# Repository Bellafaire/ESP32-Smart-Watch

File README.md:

# ESP32 Smartwatch
This project is a fully open source smartwatch based around the ESP32, the project is ongoing for updates see the hackaday.io page for this project (https://hackaday.io/project/168227-custom-smartwatch).
The goal of this project is to create a smartwatch that is easy to reprogram and use as an IOT controller or just as a DIY fashion statement.  
Serial communication and charging are handled on-board through a single micro-usb connector without any external dock. 
The watch is built around the ESP32 WROOM module and is programable using the espressif or Arduino IDE. 
Using the ESP32 allows for the user to develop their software while leveraging the open-source libraries and examples that are available online for quick development.

## Companion App 
The companion android app that allows the smartwatch to control media and obtain phone notifications has been split to a seperate repo and can be found [here](https://github.com/Bellafaire/Android-Companion-App-For-BLE-Devices) along with an example sketch for bluetooth interfacing using the ESP32. 
The app can be downloaded from the releases tab of the provided repo, the V1 watch firmware works only with app releases up to 1.2.0. 
For firmware versions 2 and 3 releases after 2.0.0 must be used, releases after this version use a different communication structure that has proved to be more reliable. 

## Firmware Versions
There are 3 versions of the firmware available for this project. Only V3 is in active development. 
The V1 firmware utilizes deep sleep along with the V1 android companion app, this firmware works well enough and offers the greatest power savings over any of the other options. 
V2 is a bit more animated, boasting some additional applications along with the switch to light sleep which enables faster wakeup from tap or by performing a wrist gesture. 

V3 is the current firmware, it is much more stable and expandable. 
The current V3 firmware supports: 
- App icons on home screen, tap to view the tagline of the notification
- Spotify control through tapping the spotify app icon
- built in calculator 
- Improved UI and tools to aid feature expansion. 

The case is 3D printed and designed in FreeCAD, the design files are available in this repo. 

### Dependencies 
If you're working with the V3 Firmware, then you will need the following dependencies, you can get these through the Arduino IDE library manager: 
- Adafruit GFX Version 1.11.9 By Adafruit
- Adafruit ST7735 and ST7789 Library Version 1.10.3 By Adafruit
- base64 Version 1.30 by Densaugeo 

Other versions of the above dependencies **will most likely work** but have not been tested on this hardware. 

## Hardware Versions
The current hardware version for the watch is V5 which provides a more slim design while maintaining all the features of V4. 

## Video Updates about the project

[Video Update #5](https://www.youtube.com/watch?v=LVs-HgjjFUM)

[Video Update #4](https://www.youtube.com/watch?v=E8-lO0pQunM)

[Video Update #3](https://www.youtube.com/watch?v=vvuce4NQqrk)

[Video Update #2](https://www.youtube.com/watch?v=UNLAq5FuJq4)

[Video Update #1](https://www.youtube.com/watch?v=IoVqdB_q3pE)

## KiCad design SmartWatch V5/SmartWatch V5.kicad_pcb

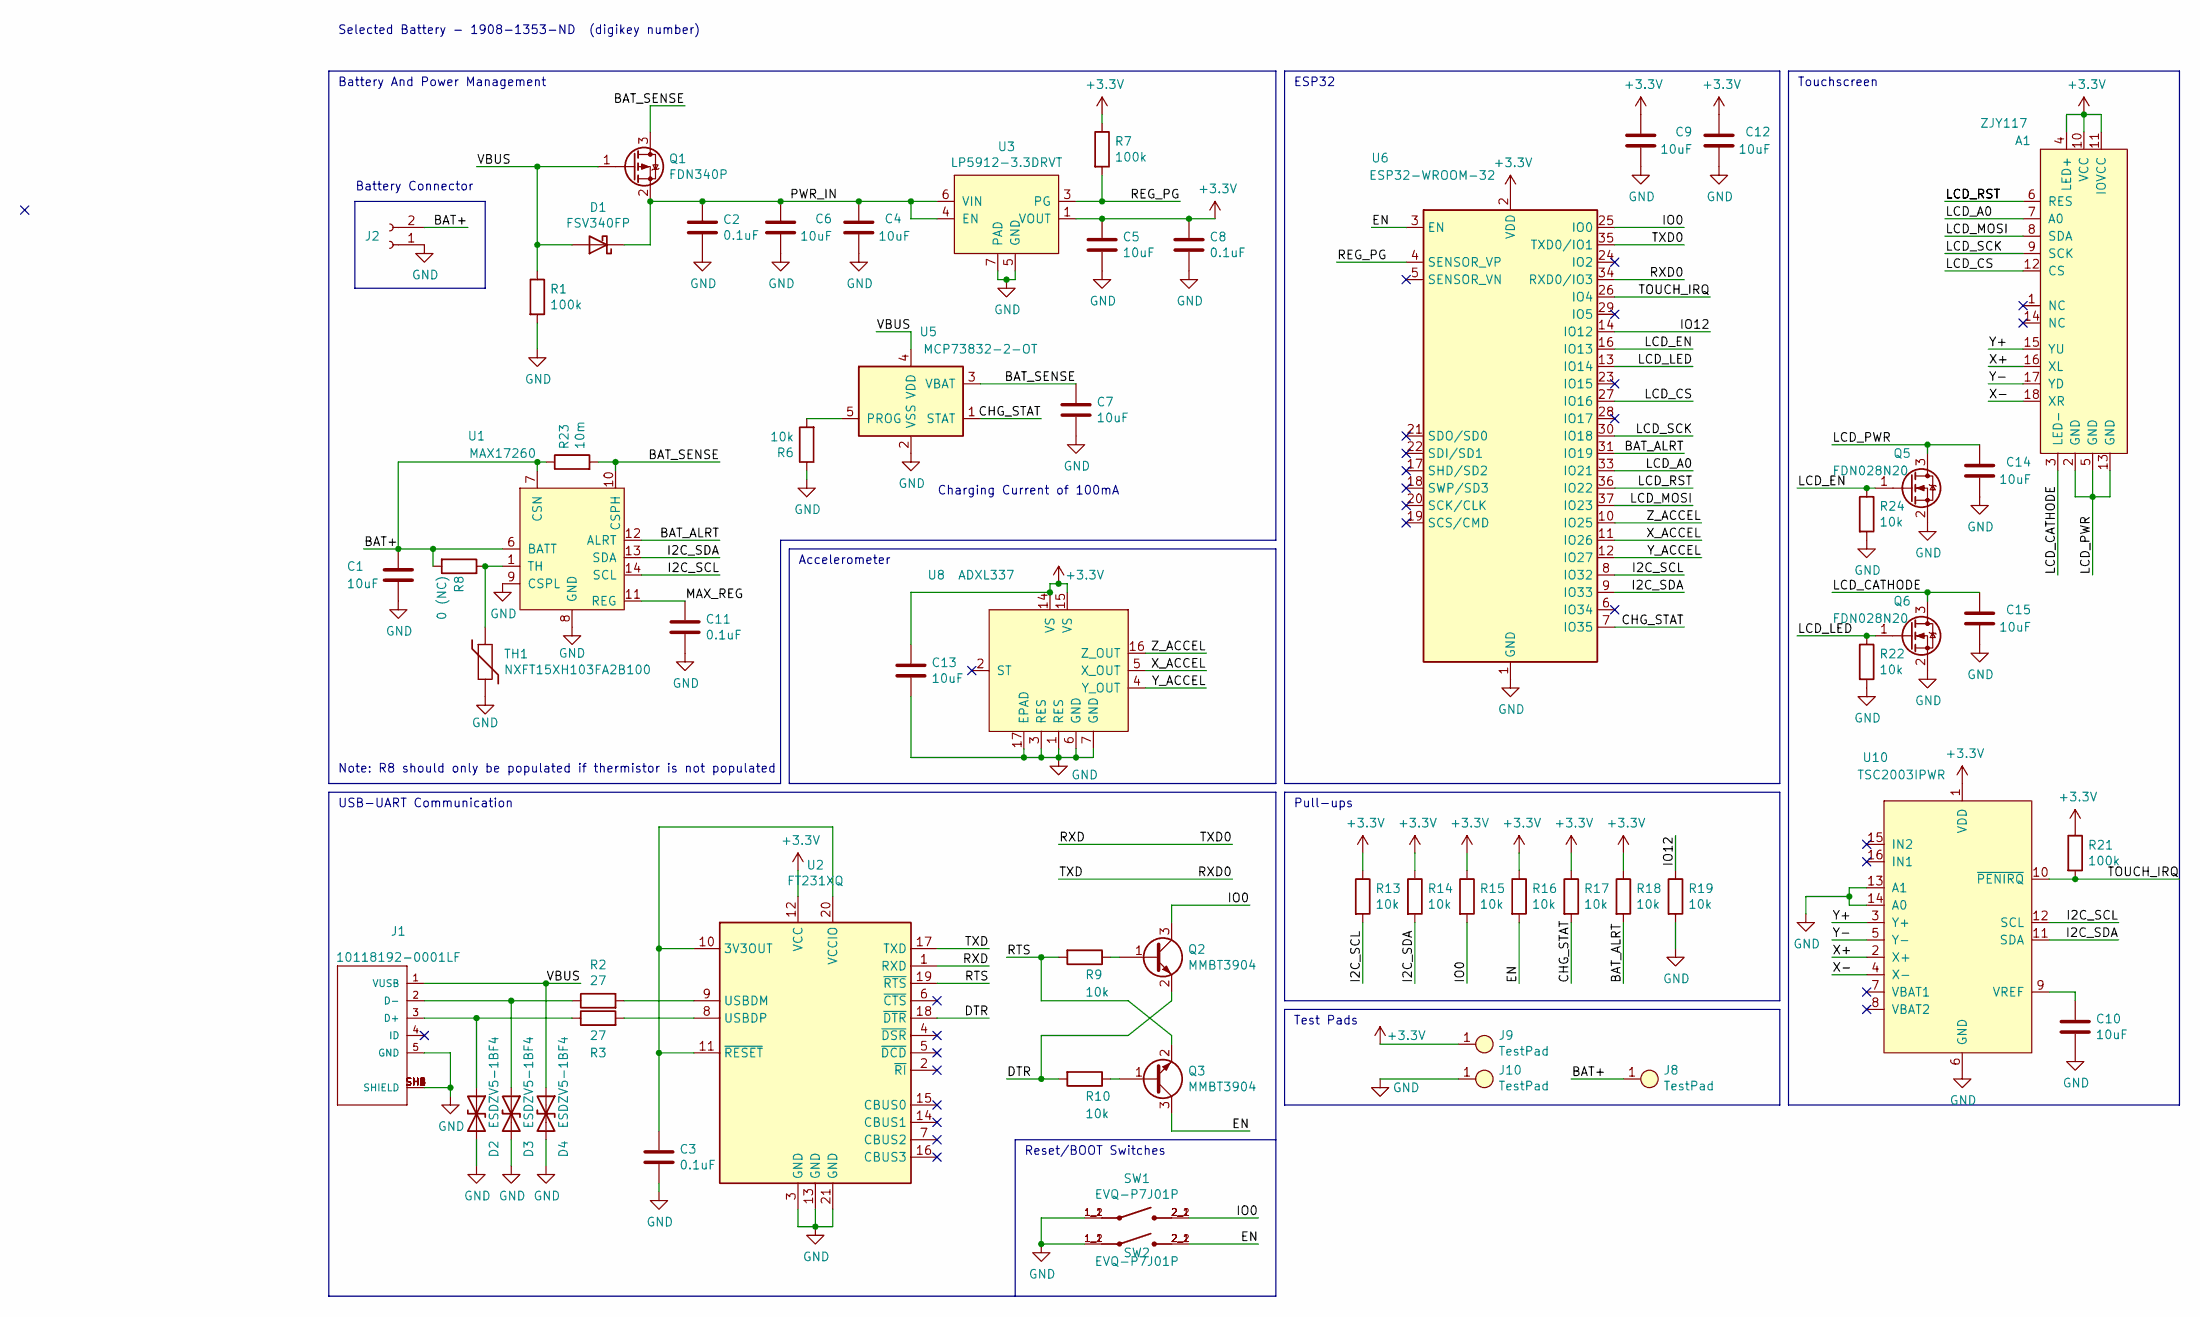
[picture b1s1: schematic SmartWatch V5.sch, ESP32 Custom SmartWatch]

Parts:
A1: ZJY117
C1, C4, C5, C6, C7, C9, C10, C12, C13, C14, C15: 10uF; C_0603_1608Metric; digikey 478-10766-1-ND
C2, C3, C8, C11: 0.1uF; C_0603_1608Metric; digikey 1276-1006-1-ND
D1: FSV340FP; D_SOD-123; digikey FSV340FPCT-ND
D2, D3, D4: ESDZV5-1BF4; D_0201_0603Metric; digikey 497-17318-1-ND
J1: 10118192-0001LF; AMPHENOL_10118192-0001LF; digikey 609-4613-1-ND
J2: BATTERY
J8, J9, J10: TestPad; TESTPAD
Q1: FDN340P; SOT-23; digikey FDN340PCT-ND
Q2, Q3: MMBT3904; SOT-23; digikey 1727-4044-1-ND
Q5, Q6: FDN028N20; SOT-23; digikey FDN028N20OSCT-ND
R1, R7, R21: 100k; R_0603_1608Metric; digikey CR0603-JW-104ELFCT-ND
R2, R3: 27; R_0603_1608Metric; digikey RMCF0603JT27R0CT-ND
R6, R9, R10, R13, R14, R15, R16, R17, R18, R19, R22, R24: 10k; R_0603_1608Metric; digikey 311-10.0KCRCT-ND
R8: 0 (NC); R_0603_1608Metric; digikey 311-0.0GRCT-ND
R23: 10m; R_0805_2012Metric; digikey RL12T.010JCT-ND
SW1, SW2: EVQ-P7J01P; SW_EVQ-P7J01P; digikey P16767CT-ND
TH1: NXFT15XH103FA2B100; PinHeader_1x02_P1.00mm_Vertical; digikey 490-5630-ND
U1: MAX17260; TDFN16-EP; digikey 175-MAX17260SEWL+TCT-ND
U2: FT231XQ; QFN-20-1EP_4x4mm_P0.5mm_EP2.5x2.5mm; digikey 768-1128-1-ND
U3: LP5912-3.3DRVT; WSON-6-1EP_2x2mm_P0.65mm_EP1x1.6mm_ThermalVias; digikey 296-44153-1-ND
U5: MCP73832-2-OT; SOT-23-5; digikey MCP73832T-2ACI/OTCT-ND
U6: ESP32-WROOM-32; digikey 1904-1010-1-ND
U8: ADXL337; ADXL337BCPZ-RL; digikey ADXL337BCPZ-RLCT-ND
U10: TSC2003IPWR; TSSOP-16_4.4x5mm_P0.65mm; digikey 296-14340-1-ND

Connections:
+3V3: A1.4 (LED+), A1.10 (VCC), A1.11 (IOVCC), C5.1, C8.1, C9.1, C12.1, C13.1, J9.1, R7.1, R13.1, R14.1, R15.1, R16.1, R17.1, R18.1, R21.1, U2.12 (VCC), U3.1 (VOUT), U6.2 (VDD), U8.14 (VS), U8.15 (VS), U10.1 (VDD)
/BAT+: C1.1, J2.2, J8.1, R8.2, R23.1, U1.6 (BATT), U1.7 (CSN)
/BAT_ALRT: R18.2, U1.12 (ALRT), U6.31 (IO19)
/BAT_SENSE: C7.1, Q1.3 (D), R23.2, U1.10 (CSPH), U5.3 (VBAT)
/CHG_STAT: R17.2, U5.1 (STAT), U6.7 (IO35)
/DTR: Q2.2 (E), R10.2, U2.18 (~DTR)
/EN: Q3.3 (C), R16.2, SW2.2_1 (2), SW2.2_2 (2), U6.3 (EN)
/I2C_SCL: R13.2, U1.14 (SCL), U6.8 (IO32), U10.12 (SCL)
/I2C_SDA: R14.2, U1.13 (SDA), U6.9 (IO33), U10.11 (SDA)
/IO0: Q2.3 (C), R15.2, SW1.2_1 (2), SW1.2_2 (2), U6.25 (IO0)
/IO12: R19.1, U6.14 (IO12)
/LCD_A0: A1.7 (A0), U6.33 (IO21)
/LCD_CATHODE: A1.3 (LED-), C15.1, Q6.3 (D)
/LCD_CS: A1.12 (CS), U6.27 (IO16)
/LCD_EN: Q5.1 (G), R24.1, U6.16 (IO13)
/LCD_LED: Q6.1 (G), R22.1, U6.13 (IO14)
/LCD_MOSI: A1.8 (SDA), U6.37 (IO23)
/LCD_PWR: A1.2 (GND), A1.5 (GND), A1.13 (GND), C14.1, Q5.3 (D)
/LCD_RST: A1.6 (RES), U6.36 (IO22)
/LCD_SCK: A1.9 (SCK), U6.30 (IO18)
/MAX_REG: C11.1, U1.11 (REG)
/PWR_IN: C2.1, C4.1, C6.1, D1.1 (K), Q1.2 (S), U3.4 (EN), U3.6 (VIN)
/REG_PG: R7.2, U3.3 (PG~), U6.4 (SENSOR_VP)
/RTS: Q3.2 (E), R9.2, U2.19 (~RTS)
/RXD: U2.1 (RXD), U6.35 (TXD0/IO1)
/RXD0: U2.17 (TXD), U6.34 (RXD0/IO3)
/TOUCH_IRQ: R21.2, U6.26 (IO4), U10.10 (~PENIRQ~)
/VBUS: D1.2 (A), D4.1 (A1), J1.1 (VUSB), Q1.1 (G), R1.1, U5.4 (VDD)
/X+: A1.16 (XL), U10.2 (X+)
/X-: A1.18 (XR), U10.4 (X-)
/X_ACCEL: U6.11 (IO26), U8.5 (X_OUT)
/Y+: A1.15 (YU), U10.3 (Y+)
/Y-: A1.17 (YD), U10.5 (Y-)
/Y_ACCEL: U6.12 (IO27), U8.4 (Y_OUT)
/Z_ACCEL: U6.10 (IO25), U8.16 (Z_OUT)
GND: C1.2, C2.2, C3.2, C4.2, C5.2, C6.2, C7.2, C8.2, C9.2, C10.2, C11.2, C12.2, C13.2, C14.2, C15.2, D2.2 (A2), D3.2 (A2), D4.2 (A2), J1.5 (GND), J1.SH1 (SHIELD), J1.SH2 (SHIELD), J1.SH3 (SHIELD), J1.SH4 (SHIELD), J1.SH5 (SHIELD), J1.SH6 (SHIELD), J2.1, J10.1, Q5.2 (S), Q6.2 (S), R1.2, R6.1, R19.2, R22.2, R24.2, SW1.1_1 (1), SW1.1_2 (1), SW2.1_1 (1), SW2.1_2 (1), TH1.2, U1.8 (GND), U1.9 (CSPL), U1.15 (EP), U2.3 (GND), U2.13 (GND), U2.21 (GND), U3.5 (GND), U3.7 (PAD), U5.2 (VSS), U6.1 (GND), U6.15 (GND), U6.38 (GND), U6.39 (GND), U8.1 (RES), U8.3 (RES), U8.6 (GND), U8.7 (GND), U8.17 (EPAD), U10.6 (GND), U10.13 (A1), U10.14 (A0)
unnamed: C3.1, U2.10 (3V3OUT), U2.11 (~RESET), U2.20 (VCCIO)
unnamed: C10.1, U10.9 (VREF)
unnamed: D2.1 (A1), J1.3 (D+), R3.1
unnamed: D3.1 (A1), J1.2 (D-), R2.1
unnamed: Q2.1 (B), R9.1
unnamed: Q3.1 (B), R10.1
unnamed: R2.2, U2.9 (USBDM)
unnamed: R3.2, U2.8 (USBDP)
unnamed: R6.2, U5.5 (PROG)
unnamed: R8.1, TH1.1, U1.1 (TH)

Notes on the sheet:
Pull-ups
Test Pads
Battery And Power Management
Battery Connector
Reset/BOOT Switches
ESP32
Touchscreen
USB-UART Communication
Charging Current of 100mA
Note: R8 should only be populated if thermistor is not populated
Selected Battery - 1908-1353-ND (digikey number)
Accelerometer

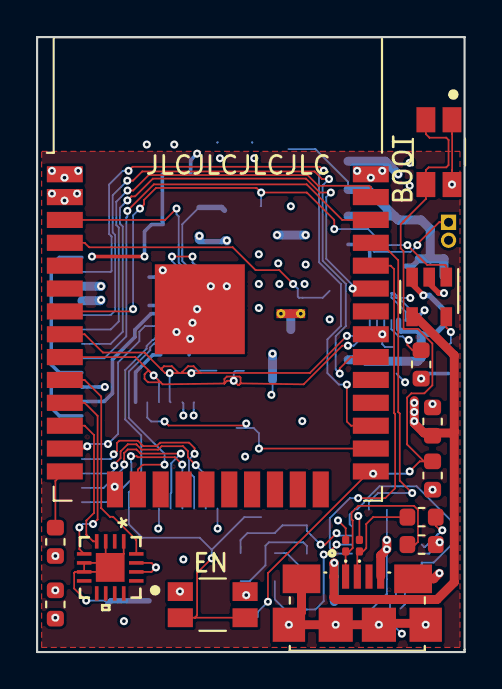
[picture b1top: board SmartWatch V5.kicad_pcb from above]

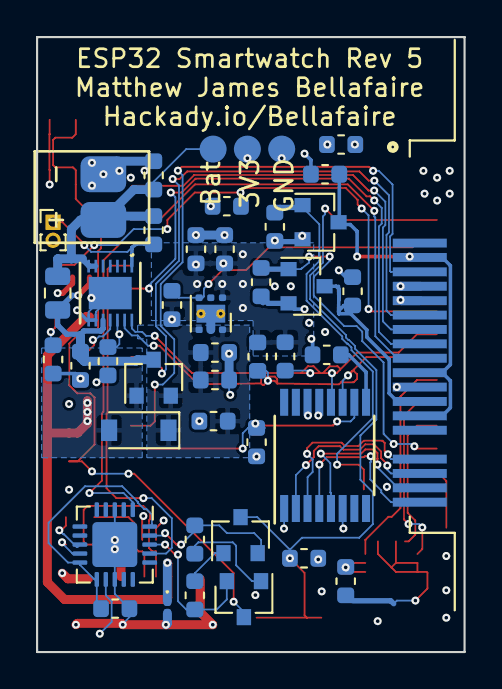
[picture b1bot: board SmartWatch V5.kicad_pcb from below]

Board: 4 copper layers, 23.7 x 34.2 mm, 59 parts (44 on the bottom side), 46 nets.

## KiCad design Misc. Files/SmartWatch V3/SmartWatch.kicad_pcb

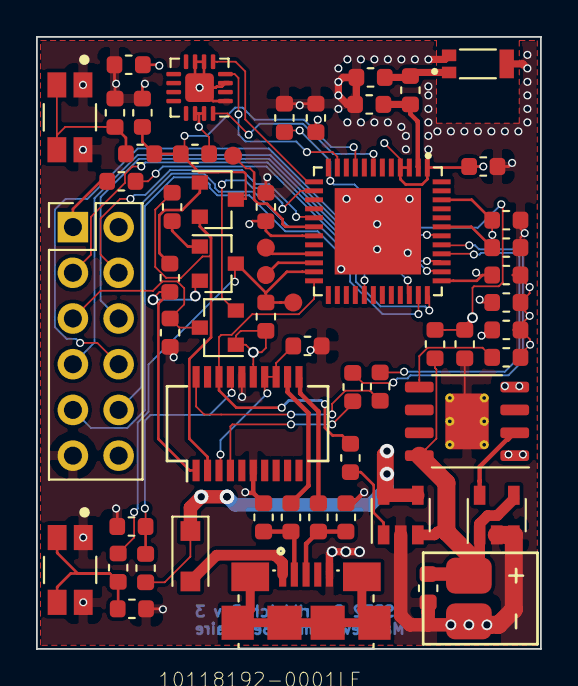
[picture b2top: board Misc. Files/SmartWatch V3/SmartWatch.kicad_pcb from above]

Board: 4 copper layers, 28.0 x 34.0 mm, 58 parts (0 on the bottom side), 48 nets.

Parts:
ANT1: W3008; ANTENNA_W3008
C1, C2: 10nF; C_0603_1608Metric
C3, C20: 10uF; C_0603_1608Metric
C4: 0.1uF; C_0603_1608Metric
C5, C7, C9, C11, C15, C16, C17, C18, C19: 0.1u; C_0603_1608Metric
C6: 0.1u (NC); C_0603_1608Metric
C8, C14: 47p; C_0603_1608Metric
C10: 10u; C_0603_1608Metric
C12, C13: TBD; C_0603_1608Metric
D2: FSV340FP; D_SOD-123F
ESP1: ESP32PICO_D4-esp32pico_d4; ESP32_D4_PICO_HAND_SOLDER
J1: 10118192-0001LF; AMPHENOL_10118192-0001LF
J2: Bat_in; BATTERY
J3, J4, J5, J6: TEST_PAD
L1: TBD; L_0603_1608Metric
Q1, Q2: MMBT3904; SOT-23
Q3: FDN340P; SOT-23
R1, R2, R3, R4, R8, R19: 0R; R_0603_1608Metric
R5, R6, R7, R11, R13, R14, R15, R16: 10k; R_0603_1608Metric
R9, R10: 27; R_0603_1608Metric
R12: 47k; R_0603_1608Metric
SW1, SW2: EVQ-P7J01P; SW_EVQ-P7J01P
U1: S-13A1A33-E8T1U3; HSOP-8-1EP_3.9x4.9mm_P1.27mm_EP2.41x3.1mm_ThermalVias
U2: LCD_TOUCH; PinHeader_2x06_P2.54mm_Vertical
U3: FT231XS; SSOP-20_3.9x8.7mm_P0.635mm
U4: MAX9065; SOT-23-5
U5: MCP73811T-420I-OT; SOT-23-5
U7: ADXL337; LFCSP-16-1EP_3x3mm_P0.5mm_EP1.6x1.6mm

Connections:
+3V3: C2.1, C3.1, C9.1, C10.1, C11.1, C16.1, C17.1, C18.1, C19.1, ESP1.1, ESP1.3, ESP1.4, ESP1.19, ESP1.37, ESP1.43, ESP1.46, Q3.1, R14.2, R15.1, U1.1, U2.12, U3.15, U7.14, U7.15
/Charge_Enable: ESP1.24, R1.1, U3.18
/ESP32 Pico D4/DTR: Q1.2, R7.1, U3.1
/ESP32 Pico D4/EN: C15.1, ESP1.9, Q2.3, R14.1, R19.1
/ESP32 Pico D4/ESP32_RX: ESP1.40, R3.2
/ESP32 Pico D4/ESP32_TX: ESP1.41, R2.2
/ESP32 Pico D4/IO0: ESP1.23, J3.1, Q1.3, R8.1, R15.2
/ESP32 Pico D4/IO2: ESP1.22, J4.1
/ESP32 Pico D4/IO12: ESP1.18, J6.1
/ESP32 Pico D4/IO15: ESP1.21, J5.1
/ESP32 Pico D4/IO32: C5.1, ESP1.12, R6.1, R11.2
/ESP32 Pico D4/LNA_IN: C13.2, ESP1.2, L1.1
/ESP32 Pico D4/RTS: Q2.2, R5.1, U3.2
/ESP32 Pico D4/RXD: R2.1, U3.4
/ESP32 Pico D4/TXD: R3.1, U3.20
/ESP32 Pico D4/USB_DN: C8.1, J1.2, R9.1
/ESP32 Pico D4/USB_DP: C14.1, J1.3, R10.2
/LCD_A0: ESP1.42, U2.8
/LCD_CS: ESP1.34, U2.3
/LCD_LED: Q3.3, R16.2, U2.5
/LCD_LED_CTRL: ESP1.14, Q3.2
/LCD_PEN: ESP1.29, R4.2
/LCD_RST: ESP1.39, U2.7
/LCD_SCK: ESP1.35, U2.9
/MISO: ESP1.38, U2.6
/MOSI: ESP1.36, U2.10
/TOUCH_CS: ESP1.17, U2.4
BAT+: C20.1, J2.2, R6.2, U1.8, U4.1, U4.4, U5.3
GND: ANT1.G1, ANT1.G2, C1.2, C2.2, C3.2, C4.2, C5.2, C6.2, C7.2, C8.2, C9.2, C10.2, C11.2, C12.2, C14.2, C15.2, C16.2, C17.2, C18.2, C19.2, C20.2, ESP1.49, J1.5, J2.1, L1.2, R11.1, R13.1, R16.1, SW1.1_1, SW1.1_2, SW2.1_1, SW2.1_2, U1.4, U1.9, U2.11, U3.6, U3.16, U4.2, U4.3, U5.2, U7.1, U7.3, U7.6, U7.7, U7.17
unnamed: ANT1.FEED, C12.1, C13.1
unnamed: C1.1, U1.5
unnamed: C4.1, U3.3, U3.13, U3.14
unnamed: C6.1, R8.2, SW1.2_1, SW1.2_2
unnamed: C7.1, R19.2, SW2.2_1, SW2.2_2
unnamed: D2.2, J1.1
unnamed: J1.SH1, J1.SH2, J1.SH3, J1.SH4, J1.SH5, J1.SH6
unnamed: Q1.1, R5.2
unnamed: Q2.1, R7.2
unnamed: R1.2, U5.1
unnamed: R4.1, U2.1
unnamed: R9.2, U3.12
unnamed: R10.1, U3.11
unnamed: R12.1, R13.2, U3.17
UV_LO: U1.2, U4.5
VUSB: D2.1, R12.2, U5.4, U5.5
X_SIG: ESP1.13, U7.5
Y_SIG: ESP1.11, U7.4
Z_SIG: ESP1.7, U7.16

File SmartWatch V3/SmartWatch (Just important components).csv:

Qty,Reference(s),Value,LibPart,Footprint,Datasheet,DigiKey Part Number
1,ANT1,W3008,SmartWatch-rescue:W3008,SmartWatch:ANTENNA_W3008,Manufacturer recommendations,553-1530-1-ND
2,"C1, C2",10nF,Device:C,Capacitor_SMD:C_0603_1608Metric,~,399-7842-1-ND
25,"C3, C20",10uF,Device:C,Capacitor_SMD:C_0603_1608Metric,~,478-10766-1-ND
50,"C5, C7, C9, C11, C15, C16, C17, C18, C19",0.1u,Device:C,Capacitor_SMD:C_0603_1608Metric,~,1276-1258-1-ND
3,ESP1,ESP32PICO_D4-esp32pico_d4,SmartWatch-rescue:ESP32PICO_D4-esp32pico_d4,SmartWatch:ESP32_D4_PICO_HAND_SOLDER,,1904-1029-1-ND
50,"Q1, Q2",MMBT3904,Transistor_BJT:MMBT3904,Package_TO_SOT_SMD:SOT-23,https://www.fairchildsemi.com/datasheets/2N/2N3904.pdf,MMBT3904TPMSCT-ND
6,"R1, R2, R3, R4, R8, R19",0R,Device:R,Resistor_SMD:R_0603_1608Metric,~,311-0.0GRCT-ND
8,"R5, R6, R7, R11, R13, R14, R15, R16",10k,Device:R,Resistor_SMD:R_0603_1608Metric,~,311-10KGRCT-ND
2,"R9, R10",27,Device:R,Resistor_SMD:R_0603_1608Metric,~,311-27.0HRCT-ND
1,R12,47k,Device:R,Resistor_SMD:R_0603_1608Metric,~,311-47GRCT-ND
10,"SW1, SW2",EVQ-P7J01P,SmartWatch-rescue:EVQ-P7J01P,SmartWatch:SW_EVQ-P7J01P,Panasonic,P16767CT-ND
2,U1,S-13A1A33-E8T1U3,SmartWatch-rescue:S-13A1A33-E8T1U3,Package_SO:HSOP-8-1EP_3.9x4.9mm_P1.27mm_EP2.41x3.1mm_ThermalVias,https://www.ablic.com/en/doc/datasheet/voltage_regulator/S13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,1662-2801-1-ND
3,U3,FT231XS,Interface_USB:FT231XS,Package_SO:SSOP-20_3.9x8.7mm_P0.635mm,http://www.ftdichip.com/Products/ICs/FT231X.html,768-1129-1-ND

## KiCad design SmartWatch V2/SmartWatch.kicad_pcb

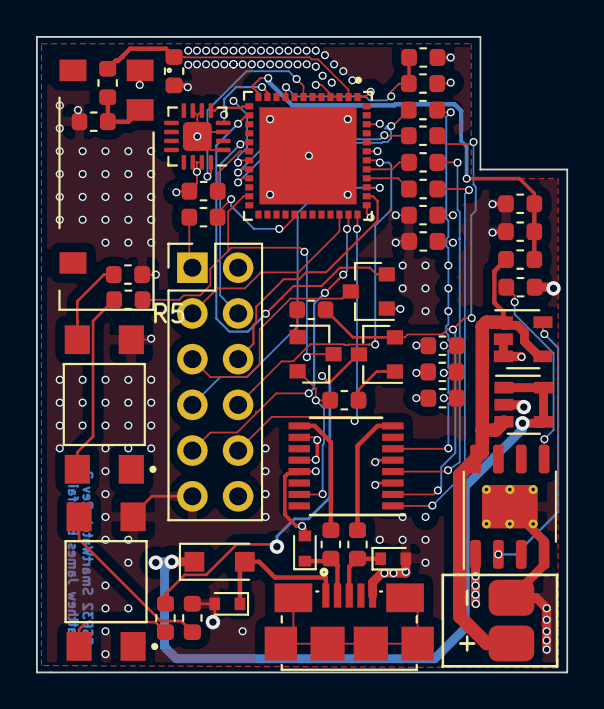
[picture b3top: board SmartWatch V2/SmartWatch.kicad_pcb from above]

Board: 4 copper layers, 29.5 x 35.3 mm, 47 parts (0 on the bottom side), 49 nets.

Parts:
C1, C2: 10nF; C_0603_1608Metric
C3: 10uF; C_0603_1608Metric
C4, C10: 10u; C_0603_1608Metric
C5, C7, C9, C11: 0.1u; C_0603_1608Metric
C6: 0.1u (NC); C_0603_1608Metric
C12: 2.7pF; C_0603_1608Metric
C13: 4.7pF; C_0603_1608Metric
D1, D3, D4: LESD5D5.0CT1G; D_SOD-523
D2: FSV340FP; D_SOD-123F
J1: 10118192-0001LF; AMPHENOL_10118192-0001LF
J2: Bat_in; BATTERY
J3: Conn_01x04; ANT_PRO-OB-440
L1: 1.6nH; L_0603_1608Metric
Q2, Q4: MMBT5551L; SOT-23
Q3: FDN340P; SOT-23
R1, R2, R13, R14: 1k; R_0603_1608Metric
R4, R8, R19: 0R; R_0603_1608Metric
R5, R7: 0(NC); R_0603_1608Metric
R6, R11, R20, R22: 10k; R_0603_1608Metric
R9, R10: 0; R_0603_1608Metric
SW4, SW5: TL3305AF260QG; SW_TL3305AF260QG
U1: S-13A1A33-E8T1U3; HSOP-8-1EP_3.9x4.9mm_P1.27mm_EP2.41x3.1mm_ThermalVias
U2: LCD_TOUCH; PinHeader_2x06_P2.54mm_Vertical
U3: FT230XS; SSOP-16_3.9x4.9mm_P0.635mm
U4: MAX9065; SOT-23-5
U5: MCP73811T-420I-OT; SOT-23-5
U7: ADXL337; LFCSP-16-1EP_3x3mm_P0.5mm_EP1.6x1.6mm
U12: ESP32-PICO-D4; PQFN50P700X700X104-49N

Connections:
+3V3: C2.1, C3.1, C4.1, C10.1, C11.1, Q3.1, R20.2, R22.1, U1.1, U2.12, U3.3, U3.10, U3.12, U7.14, U7.15, U12.1, U12.3, U12.4, U12.19, U12.37, U12.43, U12.46
/ESP32 Pico D4/CTS: R7.2, U3.6
/ESP32 Pico D4/DTR: Q4.2, R13.1, U3.15
/ESP32 Pico D4/EN: Q2.3, R19.1
/ESP32 Pico D4/IO0: Q4.3, R8.1, U12.23
/ESP32 Pico D4/IO13: R5.2, U12.20
/ESP32 Pico D4/IO15: R7.1, U12.21
/ESP32 Pico D4/IO32: C5.1, R6.1, R11.2, U12.12
/ESP32 Pico D4/IO36: U12.5, U12.6
/ESP32 Pico D4/LNA_IN: C13.1, L1.2, U12.2
/ESP32 Pico D4/RTS: Q2.2, R5.1, R14.1, U3.2
/ESP32 Pico D4/RXD: R1.1, U3.4
/ESP32 Pico D4/RXD0: R2.2, U12.40
/ESP32 Pico D4/TXD: R2.1, U3.1
/ESP32 Pico D4/TXD0: R1.2, U12.41
/ESP32 Pico D4/USB_DN: R9.2, U3.9
/ESP32 Pico D4/USB_DP: R10.1, U3.8
/LCD_A0: U2.8, U12.42
/LCD_CS: U2.3, U12.34
/LCD_LED: Q3.3, U2.5
/LCD_LED_CTRL: Q3.2, U12.14
/LCD_PEN: R4.2, U12.29
/LCD_RST: U2.7, U12.39
/LCD_SCK: U2.9, U12.35
/MISO: U2.6, U12.38
/MOSI: U2.10, U12.36
/TOUCH_CS: U2.4, U12.17
BAT+: J2.2, R6.2, U1.8, U4.1, U4.4, U5.3
GND: C1.2, C2.2, C3.2, C4.2, C5.2, C6.2, C7.2, C9.2, C10.2, C11.2, C12.2, D1.2, D3.2, D4.2, J1.5, J2.1, J3.1, L1.1, R11.1, SW4.2, SW5.2, U1.4, U1.9, U2.11, U3.5, U3.13, U4.2, U4.3, U5.2, U7.1, U7.3, U7.6, U7.7, U7.17, U12.49
unnamed: C1.1, U1.5
unnamed: C6.1, SW4.4
unnamed: C7.1, SW5.4
unnamed: C9.1, R20.1, U12.9
unnamed: C12.1, C13.2, J3.2
unnamed: D1.1, D2.2, J1.1
unnamed: D3.1, J1.2, R9.1
unnamed: D4.1, J1.3, R10.2
unnamed: J1.SH1, J1.SH2, J1.SH3, J1.SH4, J1.SH5, J1.SH6
unnamed: Q2.1, R13.2
unnamed: Q4.1, R14.2
unnamed: R4.1, U2.1
unnamed: R8.2, SW4.3
unnamed: R19.2, SW5.3
unnamed: R22.2, U12.18
UV_LO: U1.2, U4.5
VUSB: D2.1, U5.1, U5.4, U5.5
X_SIG: U7.5, U12.13
Y_SIG: U7.4, U12.11
Z_SIG: U7.16, U12.7

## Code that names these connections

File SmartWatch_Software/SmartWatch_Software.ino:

/*****************************************************************************
  The MIT License (MIT)

  Copyright (c) 2020 Matthew James Bellafaire

  Permission is hereby granted, free of charge, to any person obtaining a copy
  of this software and associated documentation files (the "Software"), to deal
  in the Software without restriction, including without limitation the rights
  to use, copy, modify, merge, publish, distribute, sublicense, and/or sell
  copies of the Software, and to permit persons to whom the Software is
  furnished to do so, subject to the following conditions:

  The above copyright notice and this permission notice shall be included in all
  copies or substantial portions of the Software.

  THE SOFTWARE IS PROVIDED "AS IS", WITHOUT WARRANTY OF ANY KIND, EXPRESS OR
  IMPLIED, INCLUDING BUT NOT LIMITED TO THE WARRANTIES OF MERCHANTABILITY,
  FITNESS FOR A PARTICULAR PURPOSE AND NONINFRINGEMENT. IN NO EVENT SHALL THE
  AUTHORS OR COPYRIGHT HOLDERS BE LIABLE FOR ANY CLAIM, DAMAGES OR OTHER
  LIABILITY, WHETHER IN AN ACTION OF CONTRACT, TORT OR OTHERWISE, ARISING FROM,
  OUT OF OR IN CONNECTION WITH THE SOFTWARE OR THE USE OR OTHER DEALINGS IN THE
  SOFTWARE.
******************************************************************************/

#include "Declarations.h"

#define uS_TO_S_FACTOR 1000000ULL /* Conversion factor for micro seconds to seconds */
#define TIME_TO_SLEEP 60         /* Time ESP32 will go to sleep (in seconds) */

RTC_DATA_ATTR int bootCount = 0;
RTC_DATA_ATTR boolean YWakeupCondition = false;
RTC_DATA_ATTR int YWakeupCount = 0;

static void RTC_IRAM_ATTR wake_stub();

static void RTC_IRAM_ATTR wake_stub() {

}

//puts device to sleep and configures wakeup sources
void deviceSleep() {
  //re-enable touch wakeup
  esp_sleep_enable_ext0_wakeup(GPIO_NUM_4, 0); //1 = High, 0 = Low
  esp_set_deep_sleep_wake_stub(&wake_stub);
  esp_deep_sleep_start();
}

void setup()
{
  unsigned long wakeupTime = micros();
  unsigned long chrono = micros();
#ifdef DEBUG
  Serial.begin(115200);
#endif
  printDebug("bootCount = " + String(bootCount));

  //init I2C communication
  Wire.begin(I2C_SDA, I2C_SCL, 100000);

  esp_sleep_wakeup_cause_t wakeup_reason;
  wakeup_reason = esp_sleep_get_wakeup_cause();

  pinMode(CHG_STAT, INPUT);
  pinMode(TOUCH_IRQ, INPUT);
  initTouch();

  EEPROM.begin(EEPROM_SIZE);

  if (getBatteryVoltage() < 3.2) {

    printDebug("Battery Voltage is too low to start device: " + String(getBatteryVoltage(), 3));
    pinMode(LCD_LED, OUTPUT);
    pinMode(LCD_EN, OUTPUT);
    digitalWrite(LCD_EN, HIGH);

    for (int a = 0; a < 3; a++) {
      digitalWrite(LCD_LED, HIGH);
      delay(100);
      digitalWrite(LCD_LED, LOW);
      delay(100);
    }



  } else {

    //the battery monitor only needs to be configured once when powered on.
    if (bootCount == 0)
    {
      notificationData[0] = 0;
      initTouch();
      initLCD();
      initBatMonitor();
      testScreen();
      tft.println("phone notifications obtained");
      //      getInternetTime();
      updateTimeFromNotificationData();
      tft.println("obtained time");

      printDebug("Battery Monitor initialized");

    }

    //Check if this is the first reboot and get ready to setup another sleep
    ++bootCount;

    switch (wakeup_reason)
    {
      case ESP_SLEEP_WAKEUP_EXT0:
        deviceActive = true;
        //if woken up by user touching screen
        initTouch();
        initLCD();
        MainLoop();
        break;
      case ESP_SLEEP_WAKEUP_EXT1:
        break;
      case ESP_SLEEP_WAKEUP_TIMER:
        break;
      default:
        printDebug("Wakeup was not caused by deep sleep: " + wakeup_reason);
        break;
    }
  }

  printDebug("Going to sleep now");

#ifdef DEBUG
  printDebug("Awake for " + String(micros() - wakeupTime) + "uS");
  Serial.flush();
#endif

  deviceSleep();
}

void loop()
{
}

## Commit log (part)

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2020-02-24 First Commit of V1 Files
2020-02-24 Commit of Rev3 Board files
    (Currently Working Board)
2020-02-24 Created new design for 3D printed case
2020-02-26 Designed Version 3.2 Case
2020-02-26 Minor changes to main body
2020-02-27 minor change to battery charge code
2020-03-10 added code to keep time in RTC
2020-03-10 changed to verison 0.0.2
2020-03-11 Added notes to schematic for rev 4 changes
2020-03-11 minor comment additions to code and schematic
2020-03-14 comment addition to schematic
2020-03-23 Completed Implementation of Touch Screen
    TODO: Final checks on circuit design
2020-04-08 Completed Electrical Schematic
2020-05-04 Completed work of schematic and board layout of revision 4
    Also began work on new body for the watch
2020-05-11 Changes to version 4 before sending off to production
2020-05-28 Edits
2020-06-05 Finished design of Rev 4.1 board and ordered
    - Also created an I2C device test program to aid assembly and future code
2020-06-15 Started work on software for the project. Basic communication with I2C devices and driving the touch screen
2020-06-15 Ported homescreen code and some interface components from V3 code into the V4 Code
2020-06-15 Implemented settings menu ported from V3
    And changed kiCad schematic to reflect the changes made to the board to resolve charging issue
2020-06-16 added indication that device is charging to the home screen
2020-06-22 Added "option select" window back from previous revision (currently disabled in code)
2020-06-28 Got android app to a semi-working state. uses standard bluetooth to forward notifications to watch
2020-06-28 Rebuilt basic notification reception
2020-06-29 Increaed data grabbed by notification reciever
2020-06-29 added 3 astriks to the end of the data transmission (important for later)
2020-06-29 Added status field and "force bt send" button for debugging purposes
2020-06-29 Fixed bluetooth causing crash and made ALL notifications appear on smartwatch
2020-06-29 Added settings option to view raw notification data
2020-06-30 Converted majority of code to using a frame buffer to draw to the screen (windows are the exception)
2020-06-30 Added background image to home screen declared in declarations as background[]
2020-06-30 added background animation to home screen
2020-07-01 Renamed the defined parameters of the circular animation to prevent future issues
2020-07-01 Added notifications page to view all data recieved about a notification
2020-07-01 popup-windows will now display text surrounded by '_' was grayed rather than the default text color
2020-07-04 Smartwatch now initiates bluetooth connection instead of waiting. Should save significant power on phone and watch
2020-07-08 Smartwatch now opens bluetooth serial as master
2020-07-13 Starting move to fully BLE based communication in companion app
2020-07-13 Android App now communicates as a BLE GATT server
2020-07-13 fixed a bug in the companion app that caused the "last update" time to not be logged
2020-07-13 minor fixes in app
2020-07-14 fixed lockup when obtaining notifications
2020-07-14 changed background notification grabbing to 60 seconds
2020-07-14 Moved BLEServer to its own class to run as a service in Android app
2020-07-14 BLEServer should more reliably detect write requests
2020-07-14 Changed smartwatch connection interval and window
2020-07-15 Remvoed unused dependencies
2020-07-15 Fixed a bug where notifications would appear twice
2020-07-15 Fixed a bug where the first notification in the list would not appear on the smartwatch
2020-07-15 Fixed notification display bug on home screen
2020-07-15 Fixed issue in notification display where notifications would be read only as ";" when they were actually null
2020-07-16 Fixed an issue where text would overflow scroll window
2020-07-17 changed background image on home screen and disabled home animation
2020-07-19 background image now displays on settings page
2020-07-19 changed selection window to prevent user double tapping options
2020-07-20 Current time is now obtained directly from android companion app, this prevents RTC drift from being an issue
2020-07-20 added more current images of the watch
2020-07-22 Removed tmp files
2020-07-22 Selection window can now scroll between multiple pages
2020-07-25 Created basic functionality to allow user to select apps
2020-07-26 Removed Folder Containing display options from earlier revisions
2020-07-28 Added capability in the android app to change songs via BLE Commands
2020-07-28 Android app no longer receives spotify notifications, alternate method will be used to read media info
2020-07-28 Smartwatch now connects to Android device in the background on startup
2020-07-28 Smartwach reads current song playing on spotify whenever the device is woken up
2020-07-28 Song title should no longer cover the apps button
2020-07-28 Moved bluetooth scanning and music related items to core 1 for stability and temporarily commented out app selection
2020-07-29 Improved BLE Communication for Media Control
2020-07-29 Removed commented out code
2020-07-29 Song title will now scroll across the bottom when it's too long
2020-07-29 Increased Transmit power in android app
2020-07-29 connect task should now terminate if device disconnects
2020-07-29 Moved BLE variables to declarations
2020-07-29 Smartwatch should now properly disconnect client when going to sleep
2020-07-29 connectToSever should now only trigger when the correct device is found
2020-08-03 Added image of project
2020-08-03 Began Hardware redesign for revision 5
    - Edited LCD schematic symbol
    - removed secondary LDO
    - changed LCD over to being switched by n channel mosfet
    - Accelerometer can now be selectively switched on
2020-08-03 Added Optional Thermistor for battery monitor
2020-08-03 Added datasheet for 2n7002K
2020-08-03 Added Surge/ESD protection to USB port
2020-08-03 Added footprint for Thermistor
2020-08-03 Removed 0 ohm jumpers on UART connection
2020-08-04 Layout Work on Rev 5
2020-08-04 Increased Android BLE TX Power (again)
2020-08-04 added "play spotify" option to apps menu
2020-08-04 Completed Rev 5 Board Layout and Routing
2020-08-05 Completed New Layout and Routing of Rev 5 (overall improved)
2020-08-05 Final Touches to Board Design
2020-08-05 Imported Cad Models to FreeCAD
2020-08-05 Board Edits
2020-08-05 Added more space between the new case's top and bottom for a better fit
2020-08-05 Rerouted ACCEL_EN to IO34
2020-08-07 Added CSV BOM and updated PDF Schematic
2020-08-08 Exported Gerber Files For Production
2020-08-10 Changed Color of Model in CAD
2020-08-10 Ripped out all BLE code for refactor
2020-08-11 Refactored BLE Connection Code
2020-08-11 Moved BLE connection forming to seperate thread (see how this goes)
2020-08-11 Abandoned Notification driven approach in android app
2020-08-11 notifications are now updated when the user taps the screen
2020-08-11 Notifications can be force updated from settings menu again
2020-08-11 Added Media controller back to homescreen (Slightly better implementation)
2020-08-11 Added "play spotify" functionality back to app menu and fixed bug with home screen play button
2020-08-12 Removed Android app from repository split off to new project - https://github.com/Bellafaire/Android-Companion-App-For-BLE-Devices
2020-08-16 Built UI for basic calculator app
2020-08-16 Calculator app no longer displays blank buttons
2020-08-16 Changed MAX17260 configuration, time-until-empty reading should be accurate now
2020-08-18 Changed Pin Declarations for Rev 5 Board
2020-08-19 Removed smartwatch backup files from showing up in git
2020-08-19 More Photos
2020-08-19 Charging is now read directly from charging IC rather than through battery monitor
2020-08-19 minor case changes
2020-08-19 Started work to make accelerometer wakeup option
2020-08-20 Value tweaking for accelerometer wakeup
2020-08-20 Screen will only stay awake while device is level when woken up by accelerometer
2020-08-21 Removed Accelerometer wakeup code implementation (too power hungry)
2020-08-29 Added "Bluetooth Serial" app which allows watch watch to be sent serial data
2020-08-31 Added MIT License Header to all software files
2020-09-01 Removed most of the window code for overhaul
2020-10-03 Modified 3D printed case to make the design more durable
2020-10-03 Added path to case for battery wires. And made more room for LCD connector
2020-11-04 Moved delcarations of eeprom data locations to the declaration files
2020-12-22 pulled in bluetooth code
2020-12-22 reimplemented timekeeping
2020-12-22 added temporary time adjustment code
2020-12-22 simple notification drawing as a temporary substitute for later improvements
2020-12-22 added MIT License header to all files
2020-12-23 some work to touch interface
2020-12-23 changes to animation circle
2020-12-23 all touch areas can now be deactivated at the same time
2020-12-28 animation circle should show connection status properly now
2021-01-01 nvm last commit fixed BLE connection issue
2021-01-02 created navigations page and transition animation
2021-01-03 Added media controls to home screen
2021-01-03 minor edits to BLE and screen-on-time
2021-01-14 Implemented Accelerometer wakeup
2021-01-15 Animation circles no longer display overtop the notification text
2021-01-15 fixed accelerometer wakeup
    edit
2021-01-15 increased threshold for accelerometer wakeup
2021-01-16 Notifications are now updated more consistently
2021-01-26 device will now reset after 3 wakes
2021-01-26 Brightened up UI and evenly applied background image across all pages
2021-01-26 Media controls now show the currently playing song when active
    edit
2021-02-04 Updated watch firmware to work with newer android companion app
2021-02-04 removed "deep sleep reset" based on boot count
2021-02-06 added non-blocking BLE receive option to allow data reception in the background (and some minor bug fixes)
2021-02-07 fixed bug where calendar would not open from navigation if BLE operation was in progress
2021-02-07 Bluetooth code will now print completed string to serial monitor when reception is complete
2021-02-23 reverted experimental bluetooth code from last commit
2021-02-24 watch will now reset when it enters sleep without a connection to reset the bluetooth peripheral.
2021-02-26 LCD Backlight will no longer flash after exiting deepsleep
2021-03-15 daylights savings
2021-03-31 Wakeup mode is now selectable from within the settings. Options are touch only, acceleromter wakeup, and time only
2021-03-31 Screen brightness can now be controlled from within the settings menu.
2021-04-27 fixed bugs with the settings menu
2021-04-27 recalibrated touch screen
    TODO: make this a process that can be performed inside the watch
2021-04-27 touch reliability improvements
2021-04-27 changed background image and corrected calculator icon
    some improvements to touch
2021-04-28 Modifications to case
2021-04-28 minor edits to lower case
2021-05-05 Device now checks notification data for spotify status instead of polling
2021-05-15 Touch ISR is now disabled before sleep, resolving an issue where the watch could stay active and drain battery
2021-09-18 watch will now get time without turning on screen if there was a reset.
2021-12-18 Started work on Rev 3 software
    (because I got bored of the old one again)
2021-12-20 Implemented touch handling for all drawables
2021-12-21 Notification viewer page improvements, and added scroll windows.
2021-12-22 added connection indicator
2021-12-25 added text and image buttons
2021-12-30 added touch calibration (rapid touch to enter)
2021-12-30 rapid touch should be less prone to accidental trigger
2022-01-13 connection status displays blue until time and notifications are updated
2022-04-24 improved deep sleep reset behavior.
2022-04-27 Settings are now stored using Preferences library instead of EEPROM library
2022-05-02 basic working application notification
2022-05-21 Notification icons with 0 notifications will now be removed from the home screen
2022-05-22 Added spotify player (opened by tapping the spotify app icon)
2022-06-20 fixes for icon transmission
2023-10-29 updated readme to include dependencies

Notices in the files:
parts and their libraries:
Copyright 2016 Accelerated Designs. All rights reserved.
